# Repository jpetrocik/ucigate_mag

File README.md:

# ucigate_mag

Hardware design and firmware to operate a UCI Starting gate.  Eagle files are avaiable in the hardware directory.  Required 3rd party libraries for compiling the firmware included in libraries directory.  These need to be copied Arudino's library directly. 

eepromburner util copies starting cadence to eprom chip on board.

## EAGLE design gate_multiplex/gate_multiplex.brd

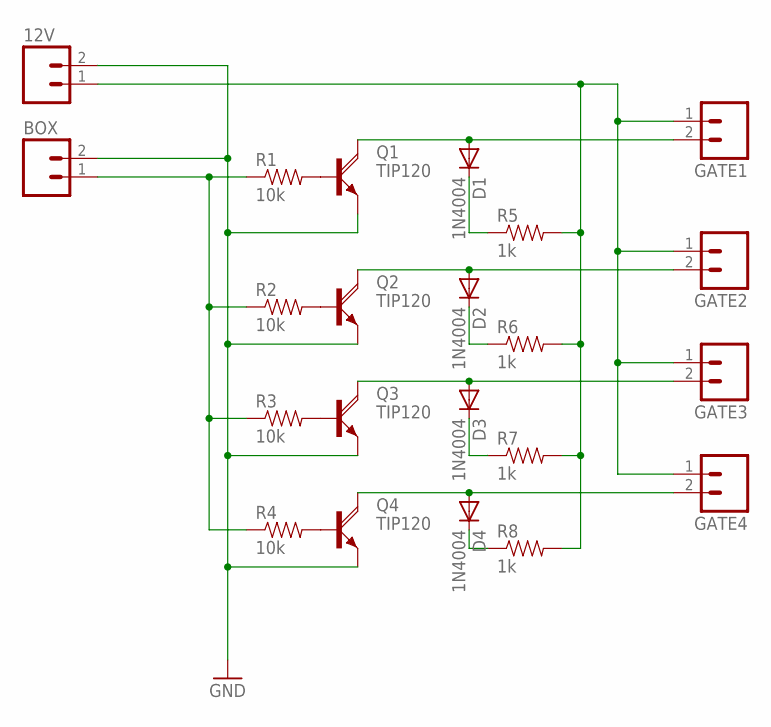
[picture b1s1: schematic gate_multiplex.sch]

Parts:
12V: M02PTH; 1X02
BOX: M02PTH; 1X02
D1, D2, D3, D4: 1N4004; DO41-10
GATE1, GATE2, GATE3, GATE4: M02PTH; 1X02
Q1, Q2, Q3, Q4: TIP120; TO220V
R1, R2, R3, R4: 10k; 1206
R5, R6, R7, R8: 1k; 1206

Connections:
GND: 12V.2, BOX.2, Q1.3 (E), Q2.3 (E), Q3.3 (E), Q4.3 (E)
unnamed: D1.A, GATE1.2, Q1.2 (C)
unnamed: D2.A, GATE2.2, Q2.2 (C)
unnamed: D3.A, GATE3.2, Q3.2 (C)
unnamed: D4.A, GATE4.2, Q4.2 (C)
unnamed: BOX.1, R1.1, R2.1, R3.1, R4.1
unnamed: Q2.1 (B), R2.2
unnamed: Q1.1 (B), R1.2
unnamed: Q3.1 (B), R3.2
unnamed: Q4.1 (B), R4.2
unnamed: 12V.1, GATE1.1, GATE2.1, GATE3.1, GATE4.1, R5.2, R6.2, R7.2, R8.2
unnamed: D1.C, R5.1
unnamed: D2.C, R6.1
unnamed: D3.C, R7.1
unnamed: D4.C, R8.1

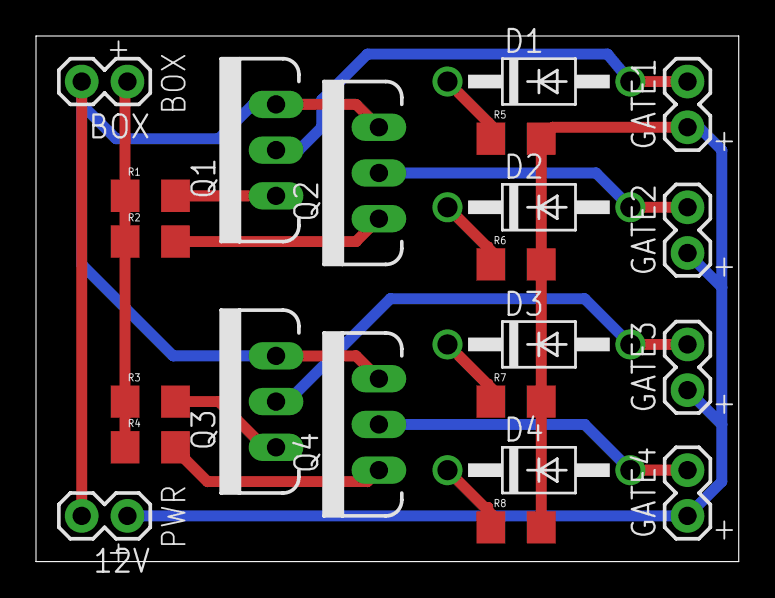
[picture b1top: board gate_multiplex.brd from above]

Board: 2 copper layers, 39.0 x 29.2 mm, 22 parts (0 on the bottom side), 15 nets.

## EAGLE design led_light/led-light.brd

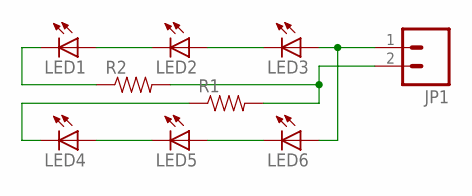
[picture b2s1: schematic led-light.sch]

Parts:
JP1: M02PTH; 1X02
LED1, LED2, LED3, LED4, LED5, LED6: LED5MM
R1, R2: RESISTORPTH-1/4W; AXIAL-0.4

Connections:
unnamed: LED1.K (C), R2.P$1 (1)
unnamed: LED2.A, LED3.K (C)
unnamed: LED1.A, LED2.K (C)
unnamed: LED4.K (C), R1.P$1 (1)
unnamed: LED4.A, LED5.K (C)
unnamed: LED5.A, LED6.K (C)
unnamed: JP1.1, LED3.A, LED6.A
unnamed: JP1.2, R1.P$2 (2), R2.P$2 (2)

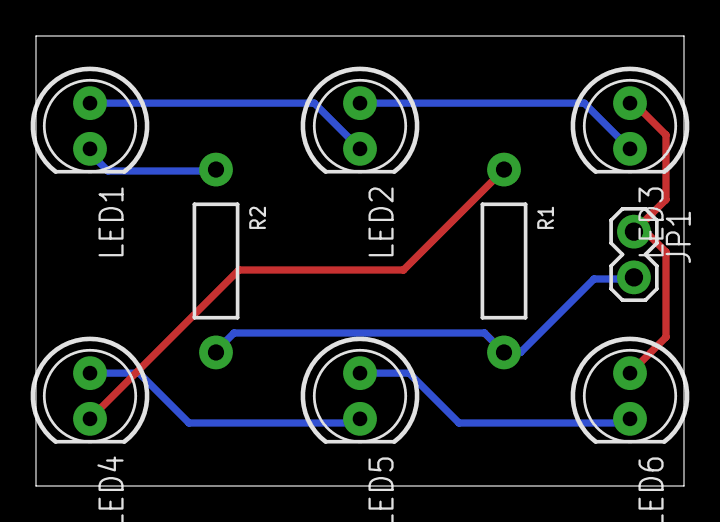
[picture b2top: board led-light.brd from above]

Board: 2 copper layers, 36.0 x 25.0 mm, 9 parts (0 on the bottom side), 8 nets.

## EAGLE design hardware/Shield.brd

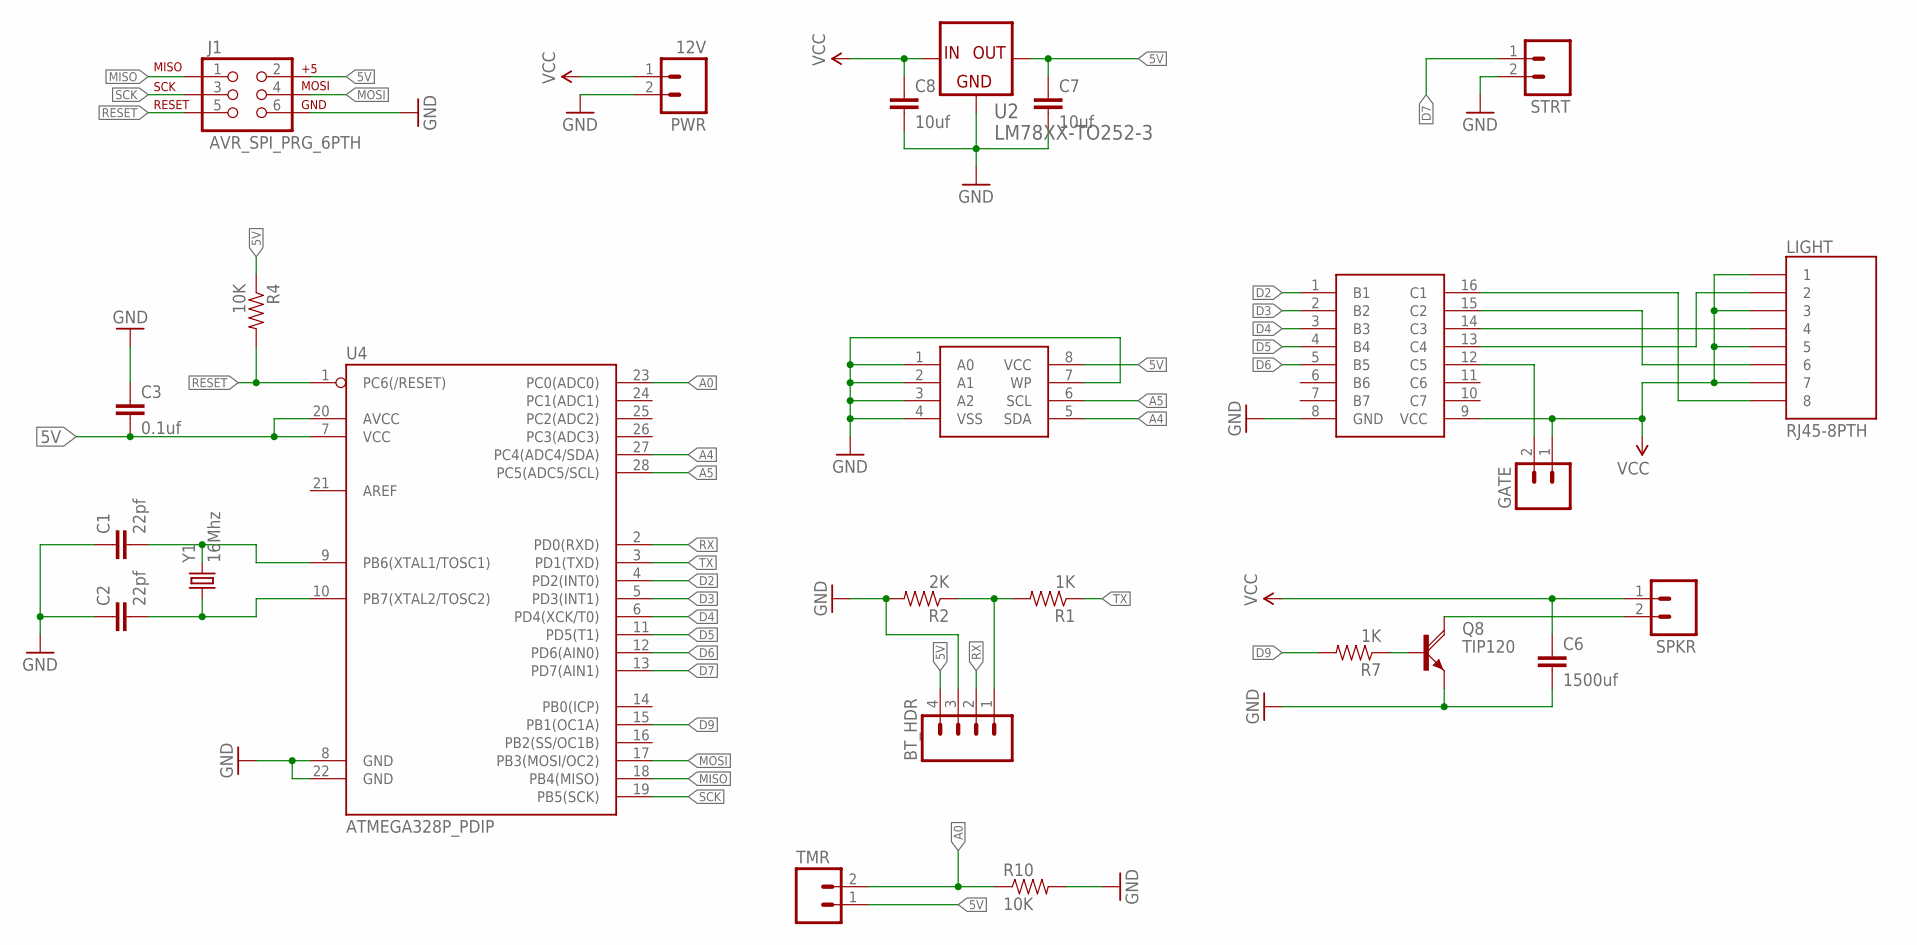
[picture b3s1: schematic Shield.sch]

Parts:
BT_HDR: M04PTH; 1X04
C1, C2: 22pf; 1206
C3: 0.1uf; 1206
C6: 1500uf; CAP-PTH-5MM
C7, C8: 10uf; CAP-PTH-SMALL
GATE: M023.5MM; SCREWTERMINAL-3.5MM-2
J1: AVR_SPI_PRG_6PTH; 2X3
LIGHT: RJ45-8PTH; RJ45-8
PWR: 12V; SCREWTERMINAL-3.5MM-2
Q8: TIP120; TO220V
R1, R7: 1K; 1206
R2: 2K; 1206
R4, R10: 10K; 1206
SPKR: M023.5MM; SCREWTERMINAL-3.5MM-2
STRT: M023.5MM; SCREWTERMINAL-3.5MM-2
TMR: M023.5MM; SCREWTERMINAL-3.5MM-2
U2: LM78XX-TO252-3; TO252-3
U4: ATMEGA328P_PDIP; DIL28-3
U$1: MC1413D; SO016
U$2: 24AAXXX; SOIC-8-EIAJ
Y1: 16Mhz; HC49US

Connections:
5V: BT_HDR.4, C3.2, C7.1, J1.2, R4.1, TMR.1, U2.3 (OUT), U4.7 (VCC), U4.20 (AVCC), U$2.8 (VCC)
A0: R10.1, TMR.2, U4.23 (PC0(ADC0))
A4: U4.27 (PC4(ADC4/SDA)), U$2.5 (SDA)
A5: U4.28 (PC5(ADC5/SCL)), U$2.6 (SCL)
D2: U4.4 (PD2(INT0)), U$1.1 (B1)
D3: U4.5 (PD3(INT1)), U$1.2 (B2)
D4: U4.6 (PD4(XCK/T0)), U$1.3 (B3)
D5: U4.11 (PD5(T1)), U$1.4 (B4)
D6: U4.12 (PD6(AIN0)), U$1.5 (B5)
D7: STRT.1, U4.13 (PD7(AIN1))
D9: R7.2, U4.15 (PB1(OC1A))
GATE: GATE.2, U$1.12 (C5)
GND: BT_HDR.3, C1.1, C2.1, C3.1, C6.2, C7.2, C8.2, J1.6, PWR.2, Q8.3 (E), R2.2, R10.2, STRT.2, U2.2 (COM), U4.8 (GND), U4.22 (GND), U$1.8 (GND), U$2.1 (A0), U$2.2 (A1), U$2.3 (A2), U$2.4 (VSS), U$2.7 (WP)
MISO: J1.1, U4.18 (PB4(MISO))
MOSI: J1.4, U4.17 (PB3(MOSI/OC2))
unnamed: BT_HDR.1, R1.2, R2.1
unnamed: LIGHT.8, U$1.16 (C1)
unnamed: LIGHT.6, U$1.15 (C2)
unnamed: LIGHT.4, U$1.14 (C3)
unnamed: LIGHT.2, U$1.13 (C4)
unnamed: Q8.2 (C), SPKR.2
unnamed: C1.2, U4.9 (PB6(XTAL1/TOSC1)), Y1.2
unnamed: Q8.1 (B), R7.1
unnamed: C2.2, U4.10 (PB7(XTAL2/TOSC2)), Y1.1
RESET: J1.5, R4.2, U4.1 (PC6(/RESET))
RX: BT_HDR.2, U4.2 (PD0(RXD))
SCK: J1.3, U4.19 (PB5(SCK))
TX: R1.1, U4.3 (PD1(TXD))
VCC: C6.1, C8.1, GATE.1, LIGHT.1, LIGHT.3, LIGHT.5, LIGHT.7, PWR.1, SPKR.1, U2.1 (IN), U$1.9 (VCC)

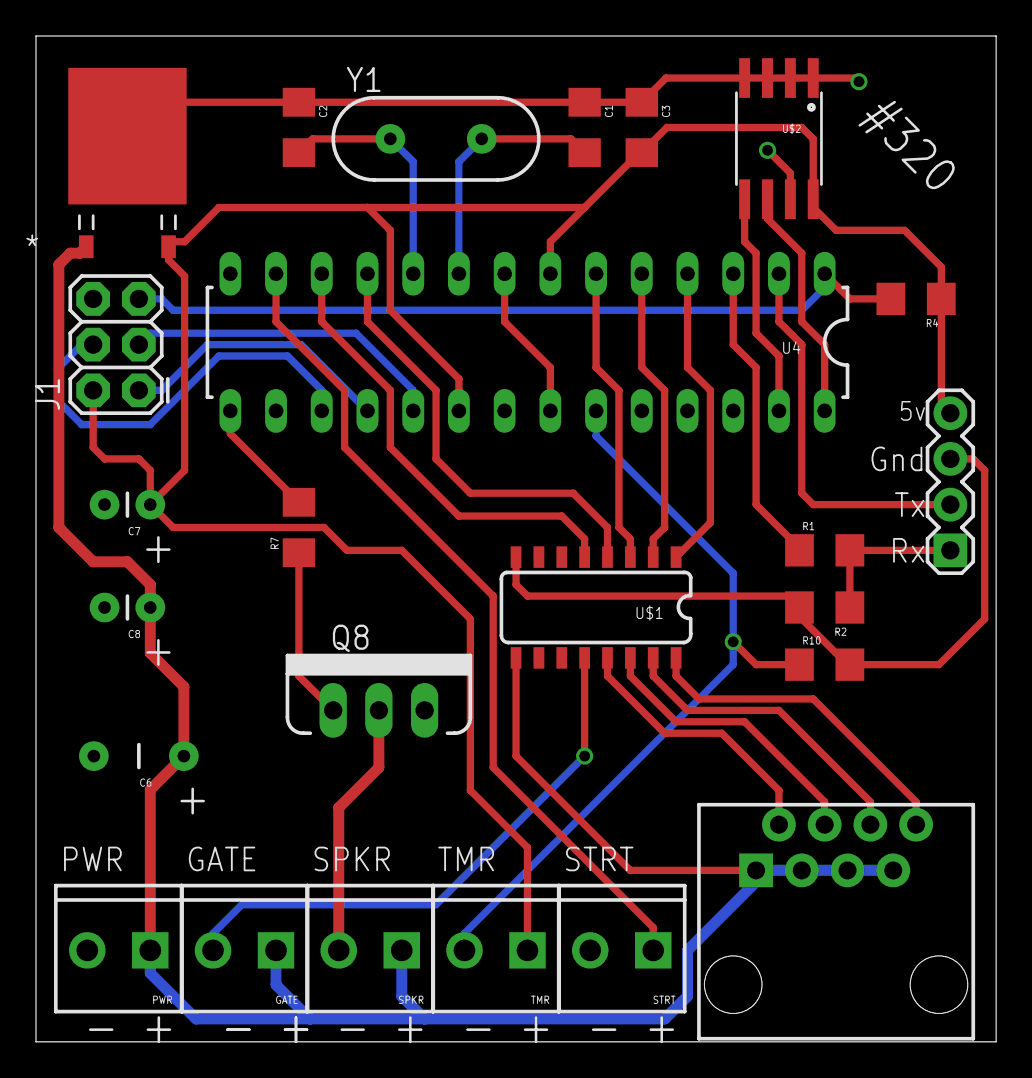
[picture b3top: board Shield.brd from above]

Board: 2 copper layers, 53.3 x 55.9 mm, 25 parts (0 on the bottom side), 29 nets.

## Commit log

2014-12-06 Rename to firmware
2016-04-12 Updared for board v3
2017-11-13 Merged to signal project for hard and firmware
2017-11-13 Switched wiring for lights to clean up board layout
2017-11-13 Adding led lights and mulitplex board
2017-11-13 Adding 3rd party libaries
2017-11-13 Adding eepromburner
2019-10-17 Formatting
2019-12-29 Adding android app

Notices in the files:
parts and their libraries:
SparkFun-Connectors: Licensing: CC v3.0 Share-Alike You are welcome to use this library for commercial purposes.
SparkFun-DigitalIC: Licensing: Creative Commons ShareAlike 4.0 International - https://creativecommons.org/licenses/by-sa/4.0
